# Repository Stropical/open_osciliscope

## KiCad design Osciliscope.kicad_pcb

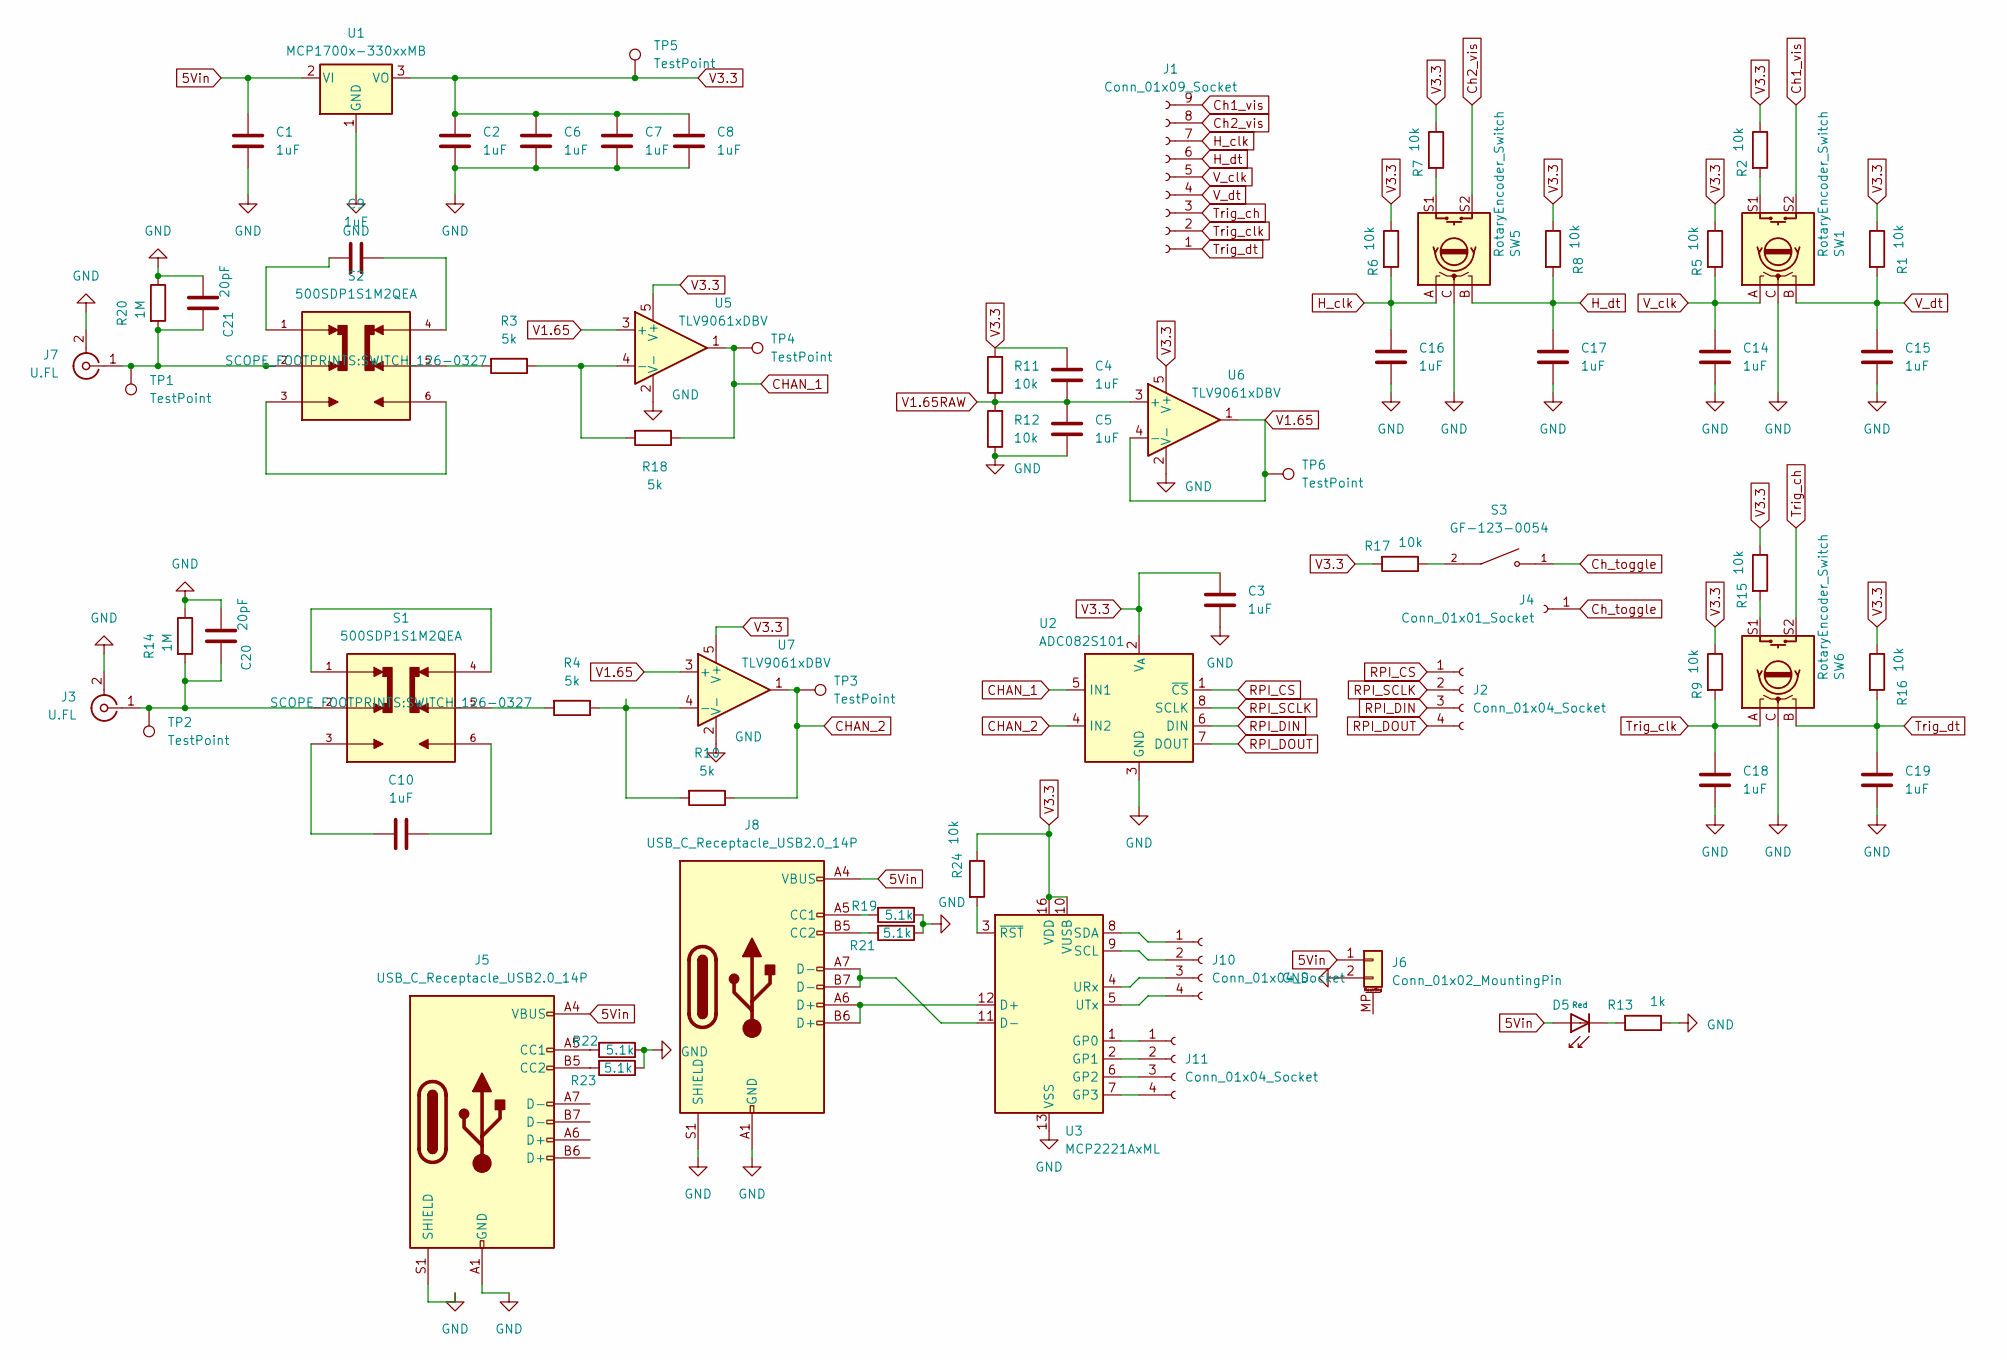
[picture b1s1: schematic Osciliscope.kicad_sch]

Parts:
C1, C2, C3, C4, C5, C6, C7, C8, C14, C15, C16, C17, C18, C19: 1uF; C_0402_1005Metric
C9, C10: 1uF; CAP_CL21_SAM
C20, C21: 20pF; C_0402_1005Metric
D5: Red; C_0603_1608Metric; Forward Voltage (VF) 1.6V~2.6V; Part NCD0805R1; LCSC C84256
J1: Conn_01x09_Socket; PinSocket_1x09_P2.00mm_Vertical
J2, J10, J11: Conn_01x04_Socket; PinHeader_1x04_P2.00mm_Vertical
J3, J7: U.FL; TE_5227671-1; LCSC C5137195
J4: Conn_01x01_Socket; PinSocket_1x01_P2.00mm_Vertical
J5, J8: USB_C_Receptacle_USB2.0_14P; USB_C_Receptacle_Amphenol_12401610E4-2A
J6: Conn_01x02_MountingPin; PinSocket_1x02_P2.00mm_Vertical
R1, R2, R5, R6, R7, R8, R9, R11, R12, R15, R16, R17, R24: 10k; RESC1608X55N
R3, R4, R10, R18: 5k; RES_CRCW_0603
R13: 1k; RC0402N_PAN
R14, R20: 1M; RC0805N_PAN
R19, R21, R22, R23: 5.1k; RC0402N_PAN
S1, S2: 500SDP1S1M2QEA; SWITCH_126-0327; PARTREV E; DigiKey_Part_Number EG2475-ND
S3: GF-123-0054; SW_GF-123-0054; PARTREV May 20, 2003; DigiKey_Part_Number CWI333-ND
SW1, SW5, SW6: RotaryEncoder_Switch; RotaryEncoder_Alps_EC11E-Switch_Vertical_H20mm
TP1, TP2, TP3, TP4, TP5, TP6: TestPoint; TestPoint_Pad_3.0x3.0mm
U1: MCP1700x-330xxMB; SOT-89-3
U2: ADC082S101; SOP65P490X110-8N
U3: MCP2221AxML; QFN-16-1EP_4x4mm_P0.65mm_EP2.5x2.5mm
U5, U6, U7: TLV9061xDBV; SOT-23-5

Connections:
5Vin: C1.1, D5.2, J5.A4 (VBUS), J5.A9 (VBUS), J5.B4 (VBUS), J5.B9 (VBUS), J6.1, J8.A4 (VBUS), J8.A9 (VBUS), J8.B4 (VBUS), J8.B9 (VBUS), U1.2 (VI)
CHAN_1: R18.1, TP4.1, U2.5 (IN1), U5.1
CHAN_2: R10.1, TP3.1, U2.4 (IN2), U7.1
Ch1_vis: J1.9, SW1.S2
Ch2_vis: J1.8, SW5.S2
Ch_toggle: J4.1, S3.1
GND: C1.2, C2.2, C3.2, C5.2, C6.2, C7.2, C8.2, C14.2, C15.2, C16.2, C17.2, C18.2, C19.2, C20.1, C21.1, J3.2 (Ext), J5.A1 (GND), J5.A12 (GND), J5.B1 (GND), J5.B12 (GND), J5.S1 (SHIELD), J6.2, J7.2 (Ext), J8.A1 (GND), J8.A12 (GND), J8.B1 (GND), J8.B12 (GND), J8.S1 (SHIELD), R12.1, R13.1, R14.1, R19.1, R20.1, R21.1, R22.1, R23.1, SW1.C, SW5.C, SW6.C, U1.1 (GND), U2.3 (GND), U3.13 (VSS), U5.2 (V-), U6.2 (V-), U7.2 (V-)
H_clk: C16.1, J1.7, R6.2, SW5.A
H_dt: C17.1, J1.6, R8.2, SW5.B
unnamed: C9.1, S2.1
unnamed: C9.2, S2.4
unnamed: C10.1, S1.3
unnamed: C10.2, S1.6
unnamed: D5.1, R13.2
unnamed: C20.2, J3.1 (In), R14.2, S1.2, TP2.1
unnamed: J5.A5 (CC1), R22.2
unnamed: J5.B5 (CC2), R23.2
unnamed: C21.2, J7.1 (In), R20.2, S2.2, TP1.1
unnamed: J8.A5 (CC1), R19.2
unnamed: J8.B5 (CC2), R21.2
unnamed: J10.1, U3.8 (SDA)
unnamed: J10.2, U3.9 (SCL)
unnamed: J10.3, U3.4 (URx)
unnamed: J10.4, U3.5 (UTx)
unnamed: J11.1, U3.1 (GP0)
unnamed: J11.2, U3.2 (GP1)
unnamed: J11.3, U3.6 (GP2)
unnamed: J11.4, U3.7 (GP3)
unnamed: R2.2, SW1.S1
unnamed: R3.2, S2.5
unnamed: R4.2, S1.5
unnamed: R7.2, SW5.S1
unnamed: R15.2, SW6.S1
unnamed: R17.1, S3.2
unnamed: S1.1, S1.4
unnamed: S2.3, S2.6
unnamed: J8.A6 (D+), J8.B6 (D+), U3.12 (D+)
unnamed: J8.A7 (D-), J8.B7 (D-), U3.11 (D-)
unnamed: R24.2, U3.3 (~RST)
unnamed: R3.1, R18.2, U5.4 (-)
unnamed: R4.1, R10.2, U7.4 (-)
RPI_CS: J2.1, U2.1 (~CS)
RPI_DIN: J2.3, U2.6 (DIN)
RPI_DOUT: J2.4, U2.7 (DOUT)
RPI_SCLK: J2.2, U2.8 (SCLK)
Trig_ch: J1.3, SW6.S2
Trig_clk: C18.1, J1.2, R9.2, SW6.A
Trig_dt: C19.1, J1.1, R16.2, SW6.B
V1.65: TP6.1, U5.3 (+), U6.1, U6.4 (-), U7.3 (+)
V1.65RAW: C4.2, C5.1, R11.1, R12.2, U6.3 (+)
V3.3: C2.1, C3.1, C4.1, C6.1, C7.1, C8.1, R1.1, R2.1, R5.1, R6.1, R7.1, R8.1, R9.1, R11.2, R15.1, R16.1, R17.2, R24.1, TP5.1, U1.3 (VO), U2.2 (V_{A}), U3.10 (VUSB), U3.16 (VDD), U5.5 (V+), U6.5 (V+), U7.5 (V+)
V_clk: C14.1, J1.5, R5.2, SW1.A
V_dt: C15.1, J1.4, R1.2, SW1.B

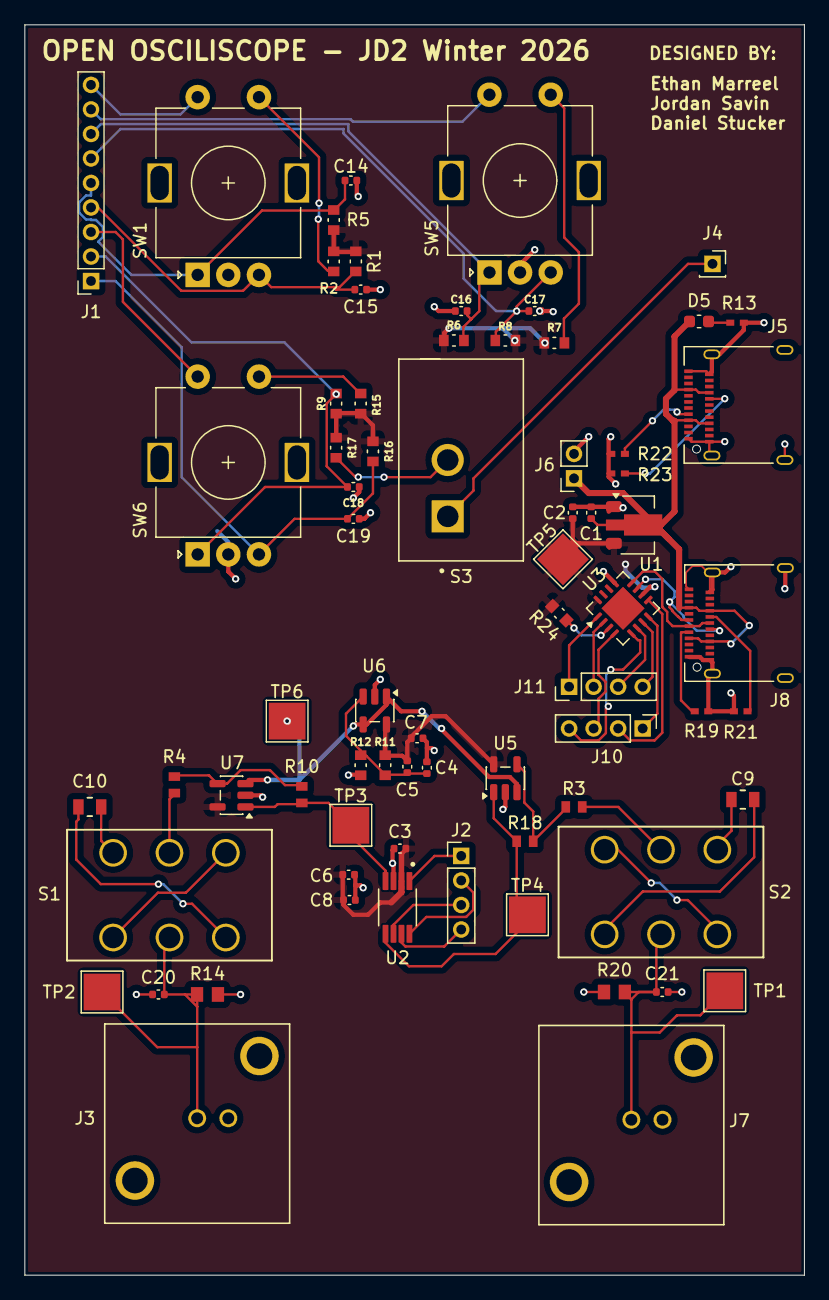
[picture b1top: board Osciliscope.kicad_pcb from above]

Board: 2 copper layers, 63.6 x 102.0 mm, 71 parts (0 on the bottom side), 53 nets.

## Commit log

2026-01-22 Add USB-C & Power
2026-01-22 Added random thing
2026-01-22 Labelled some stuff
2026-01-22 Added USB and SWD
2026-01-23 Brick all of it
2026-01-27 Added LDO with cap filtering
    This is what I think will work for our application since we don't need to run very much off of it
2026-01-29 updated volt reg
    updated volt reg
2026-01-29 updates to volt reg again
2026-02-05 Controls KiCAD
    Added folder for controls block in KiCAD. I found a model, will check dims but I also have a schem so no need to go measuring myself lol.
2026-02-05 first footprint added
    + some other stuff for controls
2026-02-05 component values
    :P
2026-02-06 Changes to voltreg
2026-02-06 New ADC
2026-02-06 added cap to voltreg
2026-02-06 updated controls schem
    full design incorporated.
    still needs full PCB layout and footprints
2026-02-06 Correct op amp
2026-02-06 Basic PCB
2026-02-06 BOM Setup
2026-02-07 analog front end design start
2026-02-07 test
2026-02-10 Added new op amp design
2026-02-11 PCB design
2026-02-11 Actual pcb changes
2026-02-11 footprint stuff
2026-02-11 USBC PD
2026-02-11 Delete
2026-02-11 Add gitignore
2026-02-11 Reorient film mask
2026-02-11 Improvment
2026-02-11 Added footprint folder
2026-02-11 forgot to save the schematic lol
2026-02-11 more small changes
2026-02-11 Revert "forgot to save the schematic lol"
    This reverts commit 07f5faf1676d518d9647f621f39270092870860e.
2026-02-11 encoder circuit added to main
2026-02-11 Balls
2026-02-11 sockets for connectors
2026-02-11 pcb update
2026-02-11 PCB Fixed
2026-02-12 front end improvements
2026-02-12 updates to schematic
2026-02-13 more changes to circuit diagram
2026-02-13 LTSpice File
    front end simulation
2026-02-13 DOUBLE POWAH
2026-02-15 Revert "DOUBLE POWAH"
    This reverts commit d7c18ef275ed38aaaeedcd9803d9307ce1c33910.
2026-02-16 changes to lots of stuff
2026-02-17 added footprint for bnc
2026-02-17 Footprint updates
2026-02-17 Add USB stuff
2026-02-17 pcb changes
2026-02-17 PCB updaes
2026-02-17 pcb board rules update
2026-02-17 PCB Updates
2026-02-18 pcb updates and footprints
2026-02-18 more updates
2026-02-18 idk anymore
2026-02-18 Resistor, BNC, DPDT, C50V footprints
2026-02-18 footprints populated to PCB
    there is an error tho lol
2026-02-18 Routed
2026-02-18 Silkscreen
2026-02-18 pcb silkscreen edits
2026-02-18 Single Pin Lol
2026-02-18 almost final changes
2026-02-18 Fixed all PCB DRC errors
    we still have all footprint related warnings
2026-02-18 final changes....probably
2026-02-18 final push
